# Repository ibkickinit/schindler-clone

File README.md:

# Schindler 2.0

A modern FPGA-based replacement for the Cal Media **Schindler MVPHD-24** — a 24fps video frame rate converter used to drive CRT monitors that appear in film shots. Roughly 75 MVPHD-24 units remain in service worldwide; this project is a from-scratch alternative scoped to modern workflows.

## Scope

- **Input:** HDMI + Composite + Component (with optional broadcast-tier SDI video IN/OUT/loop-through)
- **Output:** Composite + Component (YPbPr) + S-Video, driving 1970s consumer CRTs and broadcast monitors (Sony PVM/BVM); HDMI out for confidence monitoring or live output
- **Genlock:** to film camera reference (LTC, tri-level, black burst, word clock); SDI ref with VITC extraction
- **Frame rates:** 23.976, 24.000, 25.000, 29.97, 30.000, 47.95, 48.000, 50, 59.94, 60 fps (with 60 Hz → 50 Hz cadence conversion for cross-region content)
- **Color pipeline:** ported from the Screenie/NovaTool codebase
- **Control:** dual-band WiFi (concurrent AP + STA) + BLE setup pairing + GbE; web UI hosted on the Zynq PS under PetaLinux
- **Front panel:** 2.8-3.5" color TFT + rotary encoders + hardware buttons + status LEDs (no touchscreen)
- **Rear panel:** 2.2" color TFT (port status, 1Hz refresh) + port status LEDs (no touchscreen)
- 
## Why

The Schindler is unobtainable, expensive when found, and lacks modern color/EDID/web workflows. The market is small but underserved: rental houses, DPs shooting on CRTs, and music-video / period productions.

## Status

Early prototype phase, hardware ordered. See [`docs/01-spec.md`](docs/01-spec.md) for current spec & backlog and [`docs/schindler-playbook.md`](docs/schindler-playbook.md) for the development narrative.

## Hardware

### Development
- Digilent Zybo Z7-20 — FPGA bring-up (Zynq-7020 silicon, matches production target)
- STM32H735G-DK — UI MCU + TFT bench development
- Oscilloscope — signal analysis

### Production architecture
- Trenz TE0720 SOM — Zynq-7020 industrial (-40 to +85 °C), on custom carrier
- STM32H735IGT6 — dedicated front-panel UI MCU
- RP2040 + Si5351 — genlock PLL subsystem
- ADV7393 — composite/component/S-Video output DAC
- ADV7280 — composite/component input decoder
- Semtech GS3470 — SDI receiver (ref + optional broadcast video input)
- Semtech GS2962 — SDI transmitter (broadcast tier)
- Laird Sterling LWB5+ — pre-certified dual-band WiFi/BT module
- Custom 6-8 layer carrier PCB
- 1RU rack chassis

## License

TBD

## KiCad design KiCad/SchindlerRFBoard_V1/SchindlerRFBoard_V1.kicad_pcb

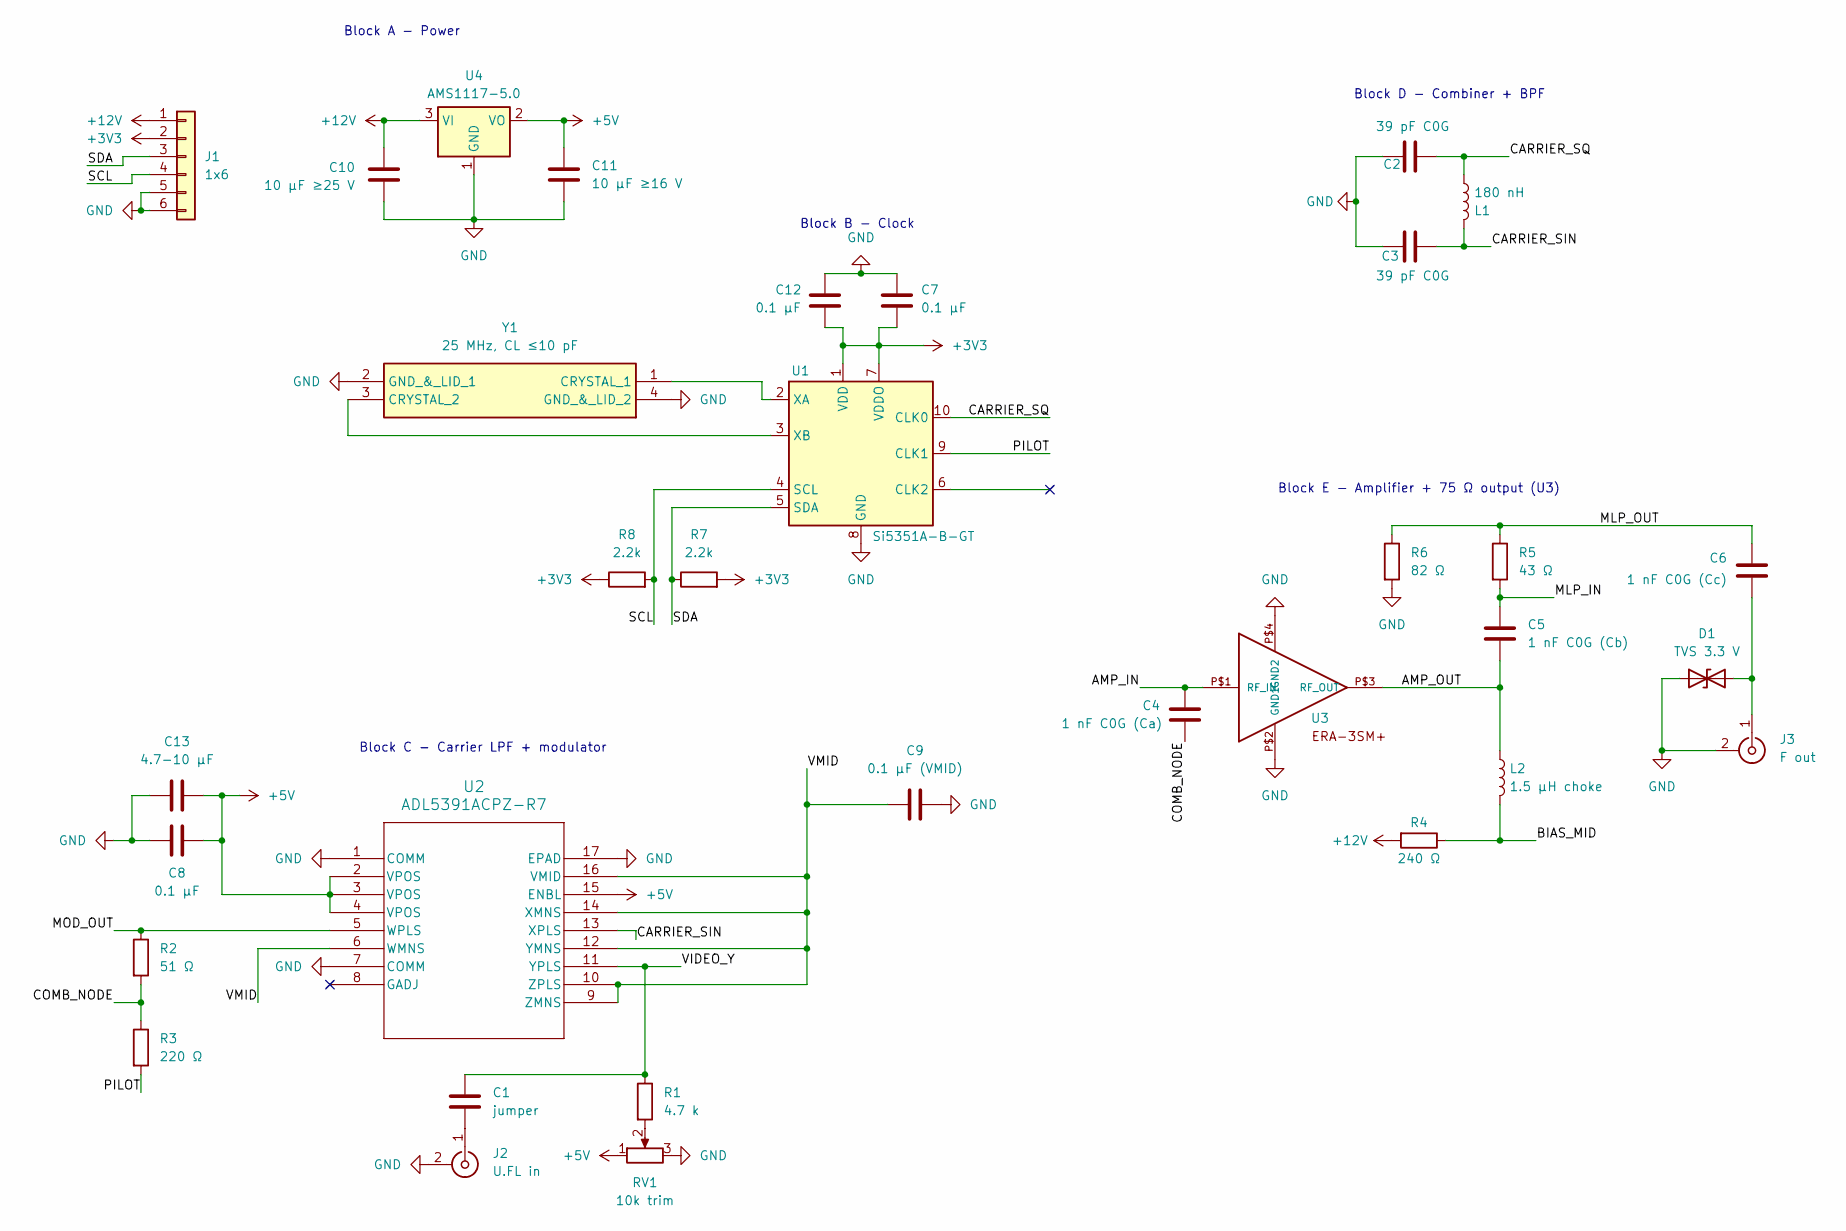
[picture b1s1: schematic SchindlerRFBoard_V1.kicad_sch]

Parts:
C1: jumper; C_0805_2012Metric
C2, C3: 39 pF C0G; C_0805_2012Metric
C4: 1 nF C0G (Ca); C_0805_2012Metric
C5: 1 nF C0G (Cb); C_0805_2012Metric
C6: 1 nF C0G (Cc); C_0805_2012Metric
C7, C8, C12: 0.1 µF; C_0805_2012Metric
C9: 0.1 µF (VMID); C_0805_2012Metric
C10: 10 µF ≥25 V; C_0805_2012Metric
C11: 10 µF ≥16 V; C_0805_2012Metric
C13: 4.7-10 µF; C_0805_2012Metric
D1: TVS 3.3 V; D_SOD-323
J1: 1x6; PinHeader_1x06_P1.00mm_Vertical
J2: U.FL in; U.FL_Hirose_U.FL-R-SMT-1_Vertical
J3: F out; U.FL_Hirose_U.FL-R-SMT-1_Vertical
L1: 180 nH; L_0805_2012Metric
L2: 1.5 µH choke; L_0805_2012Metric
R1: 4.7 k; R_0805_2012Metric
R2: 51 Ω; R_0805_2012Metric
R3: 220 Ω; R_0805_2012Metric
R4: 240 Ω; R_0805_2012Metric
R5: 43 Ω; R_0805_2012Metric
R6: 82 Ω; R_0805_2012Metric
R7, R8: 2.2k; R_0805_2012Metric
RV1: 10k trim; Potentiometer_Bourns_3296W_Vertical
U1: Si5351A-B-GT; MSOP-10_3x3mm_P0.5mm
U2: ADL5391ACPZ-R7; CP_16_27_ADI
U3: ERA-3SM+; WW107
U4: AMS1117-5.0; SOT-223-3_TabPin2
Y1: 25 MHz, CL ≤10 pF; LFXTAL072604; Manufacturer_Part_Number LFXTAL072604

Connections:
+3V3: C7.2, C12.2, J1.2, R7.2, R8.1, U1.1 (VDD), U1.7 (VDDO)
+5V: C8.1, C11.1, C13.1, RV1.1, U2.2 (VPOS), U2.3 (VPOS), U2.4 (VPOS), U2.15 (ENBL), U4.2 (VO)
+12V: C10.1, J1.1, R4.2, U4.3 (VI)
/AMP_IN: C4.2, U3.P$1 (RF_IN)
/AMP_OUT: C5.2, L2.1, U3.P$3 (RF_OUT)
/BIAS_MID: L2.2, R4.1
/CARRIER_SIN: C3.2, L1.2, U2.13 (XPLS)
/CARRIER_SQ: C2.1, L1.1, U1.10 (CLK0)
/COMB_NODE: C4.1, R2.2, R3.1
/MLP_IN: C5.1, R5.2
/MLP_OUT: C6.1, R5.1, R6.1
/MOD_OUT: R2.1, U2.5 (WPLS)
/PILOT: R3.2, U1.9 (CLK1)
/SCL: J1.4, R8.2, U1.4 (SCL)
/SDA: J1.3, R7.1, U1.5 (SDA)
/VIDEO_Y: C1.1, R1.1, U2.11 (YPLS)
/VMID: C9.1, U2.6 (WMNS), U2.9 (ZMNS), U2.10 (ZPLS), U2.12 (YMNS), U2.14 (XMNS), U2.16 (VMID)
GND: C2.2, C3.1, C7.1, C8.2, C9.2, C10.2, C11.2, C12.1, C13.2, D1.1 (A1), J1.5, J1.6, J2.2 (Ext), J3.2 (Ext), R6.2, RV1.3, U1.8 (GND), U2.1 (COMM), U2.7 (COMM), U2.17 (EPAD), U3.P$2 (GND1), U3.P$4 (GND2), U4.1 (GND), Y1.2 (GND_&_LID_1), Y1.4 (GND_&_LID_2)
unnamed: C6.2, D1.2 (A2), J3.1 (In)
unnamed: C1.2, J2.1 (In)
unnamed: R1.2, RV1.2
unnamed: U1.2 (XA), Y1.1 (CRYSTAL_1)
unnamed: U1.3 (XB), Y1.3 (CRYSTAL_2)

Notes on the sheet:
Block E - Amplifier + 75 Ω output (U3)
Block C - Carrier LPF + modulator
Block B - Clock
Block D - Combiner + BPF
Block A - Power

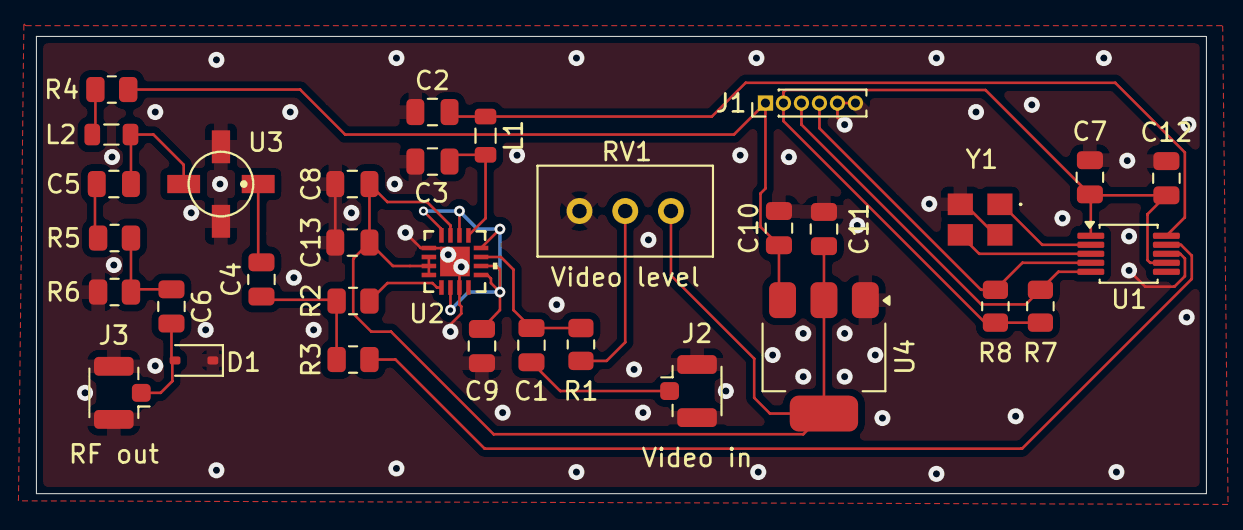
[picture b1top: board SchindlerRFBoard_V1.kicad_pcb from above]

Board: 2 copper layers, 65.0 x 25.4 mm, 33 parts (0 on the bottom side), 23 nets.

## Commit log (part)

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2026-06-04 docs(manifest): build #28 — Mackin blend engages on silicon (BLEND 60/60, DDR holds)
2026-06-05 fix(geometry): signed window translation (off-screen shift) + restore scale anchor
    Replaces #29's source-crop pan with the behavior actually requested:
    - Position is a SIGNED output-window origin: shift can push the image clean off
    the left/top edge (pixels leave the frame, matte fills the opposite edge), at
    ANY scale incl. 100%. pg_addrgen membership compares are now signed.
    - src_col0/src_row0 become the DDA seed = source col/row at the first on-screen
    pixel; firmware derives it from the off-screen amount. Same formula yields the
2026-06-05 docs(manifest): build #31 ✅ CLEAN 3-boot — closes owed #28 Mackin; #30 verified; #106 gate clear
2026-06-05 fix(daemon): send 'P' flip cmd only on flip change — kills redundant 2nd geometry write during size/shift drags
2026-06-05 fix(#110): color-temp neutral = D65 6500K (video/display white), not 5600 — rebalance ladder around D65
2026-06-05 fix(#111): Freeze un-freeze — re-arm S2MM VSIZE on resume (RS alone doesn't restart a halted VDMA)
2026-06-05 feat(#112 Phase-3): wire gamma_lut into color pipeline + load path + presets
    BD: splice gamma_lut_0 after color_matrix_0 -> axis_to_vid_io_0 (build_phase_b); add gamma
    load GPIO axi_gpio_11 @ M14 (NUM_MI 14->15) + slices (bypass/tog/ch/addr/data) wired to
    gamma_lut_0 (readengine_b_bd). Firmware: GAMMA_GPIO_BASE + gamma 1.8/2.2/2.4 preset LUTs
    (precomputed, libm-free) + toggle-strobed loader + 'O g <0|18|22|24>'. Daemon operator.set
    gamma; UI Gamma Off/1.8/2.2/2.4 buttons. Default GPIO bypass=1 (transparent at boot).
    YCbCr matrix preset deferred (analog-only, would break HDMI RGB; trivial future color_matrix preset).
2026-06-05 fix(#112): gamma — on-device fixed-point curve, kill bulk UART transport (corruption fix)
    The bulk LUT load ('O G' 262-char line) corrupted under the periodic status-print bursts
    that block the UART poll → RX FIFO overflow → garbage curve (crush+speckle). Replace with
    on-device fixed-point pow: daemon sends only 'O g <gamma*10>' (short, robust); firmware
    computes out[i]=round(255*(i/255)^(1/g)) via Q16 integer-power + iterated-sqrt. Verified
    <=1 LSB vs float pow (g 0.5..4.0). Removed preset tables, bulk 'O G' handler, hexnib.
    Slider + presets unified on 'O g'. ELF-only (gamma_lut HDL unchanged).
2026-06-05 docs(manifest): record builds #32 (flips) / #33 (gamma, failed timing) / #34 (gamma clean) + ELF turns + open #114 read-engine gradient chroma
2026-06-05 docs(#108): 720p60-OUT column 1080-input cells verified — 1080p24→720p60 ✅ (3-boot), 1080p30→720p60 ✅; full Osee sweep (24/30/60 + 59.94/29.97 NTSC + 50/25 PAL) all lock w/ correct cadence + zero dri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
2026-06-06 fix(#114): double-buffer gamma_lut — atomic SOF bank-swap kills load chroma + restores live-drag
    Root cause (re-attributed from read engine): single-buffer loaded the LUT over the live display
    with non-atomic per-address R/B/G writes → fast/large change showed a half-updated chromatic LUT.
    Now: 2 banks (addr={bank,idx}), firmware loads the INACTIVE bank at any speed (display untouched),
    flips swap → bank goes live ATOMICALLY at next SOF. No flash, no chroma, live-drag safe.
    HDL gamma_lut.v (swap input + sof-gated rd_bank) + TB (Total errors=0: loads don't change display,
    swap only at SOF, ping-pong). Firmware gamma_put/gamma_set_byp_swap (load-to-inactive then enable+swap).
2026-06-06 feat(#107a): wire filt_mode + inv_w GPIO — firmware reciprocal + UART F 0|1|2|3
    BD: filt_h(bit27)→filt_mode GEO_C ch2 [31:30]; new axi_gpio_12 @ M15 (NUM_MI 15→16) inv_w[15:0]
    (inv_h[31:16] reserved for #107b) → pg_re_0/inv_w. Firmware: g_re_filt_mode (0..3); re_write_geometry
    computes inv_w=round((1<<16)/w) clamp 0xFFFF + writes axi_gpio_12; UART 'F 0|1|2|3' (NN/box/H-bilin/H+V).
    Completes #107a (H-bilinear) — bundle w/ #114 into next bitstream; check lerp WNS (pipeline if <0).
2026-06-06 fix(#107a): add stage R0 (register taps before lerp) — WNS -5.6 path was m3_rd_data→lerp→r_A
    #36 still failed (-5.6): the lerp fed off m3_rd_data which already carries linefetch window-extract
    combinational depth. R0 registers the raw taps + weight first, so the lerp (stage R) starts from
    registers (one multiply to r_A). +1 more ospace reserve (now 7). Sim Total errors=0. Rebuilding.
2026-06-06 feat(#114): restore live-drag gamma slider — load is race-free now, drag = clean atomic loads
    Re-enables debounced 'input' commit (live preview) now that the data-then-strobe CDC + double-buffer
    make every load reliable + atomic. Re-archived 38-720p60-gamma-bilinear with the fixed ELF (bench-validated:
    Justin confirms gamma chroma GONE, bilinear clean). Closes the #114 chroma saga.
2026-06-06 feat(#107b): BD inv_h slice (axi_gpio_12[31:16] → pg_re_0/inv_h) for V-bilinear weight
2026-06-06 feat(ui): 'Engine 1 path' reorg + maintain-aspect-ratio lock
    Reorganize the page to mirror the silicon signal chain:
    Source/Input (input range/colorspace) → Engine 1 → Output A (HDMI): Geometry&Scale · FRC · Color · Operator
    Color Temp moves into the Color group (it's the color_correct white-point, not the read engine) alongside
    the catalog Saturation/RGB/matrix + gamma — answering 'merge the color-related things'. Per-category named
    mounts (mount-color/frc/scaler) let the firmware-catalog controls render inside the matching Engine-1
    sub-group; System/Status fall back to #catalog-mount. Dual-engine build will add a parallel 'Engine 2 → Output B'.
2026-06-06 design(corrections): validate keystone + warp math (previewer) — all three proven
    tools/correction_preview.py renders keystone (projective, per-pixel /w divide → clean perspective
    trapezoid) and warp (9x9 mesh sampling the pincushion map → reproduces the parametric render, proving
    the mesh subsumes the parametric corrections). Same (ox,oy)->(sx,sy) addrgen interface as the real
    engine. All three correction maths now visually verified pre-HDL; addrgen settled, only the deferred
    engine HDL remains. Validation status recorded in the design doc.
2026-06-07 docs(engine): phased warp-engine build tracker + pg_tilecache architecture spec
    Phase 1 (pg_affine) done; Phase 2 (pg_tilecache) fully specified: tag/LRU + tile BRAM + prefetch
    walker (runs the affine DDA ahead) + AXI DataMover tile DMA + 2x2 sampler + underrun guard. 128-tile/
    384KB cache, 32x32 tiles (gate params). Phase-2 sim with a behavioral DDR = the real-time gate (assert
    output FIFO never underruns + bit-exact warp). Risks/knobs noted. Phase 5b = pincushion/keystone/warp
    addrgen variants (math pre-validated).
2026-06-07 feat(engine P2/M3a): 4-bank 1px/clock 2x2 gather — bit-exact in sim
    The hard part: returns the bilinear 2x2 in ONE cycle even across 4 tiles, via a 4-bank (x-parity x
    y-parity) tile BRAM where each parity-bank supplies exactly one neighbour; a parity mux routes banks
    to p00/p10/p01/p11, with an edge-mux for clamp-to-self frame edges. sim/pg_tilecache_rt_tb.v: 3072
    gathers over 2 passes (straddles + edges + cache hits) = 0 errors. Bug found+fixed: tag lookup was a
    function in a wire-assign (sensitive only to its arg, NOT the tag/vld arrays it reads -> fills never
    re-triggered it -> infinite re-fetch). Combinational always@* fixes it. LESSON: never put a memory-
2026-06-07 feat(engine M3c): full warp datapath integrated + end-to-end bit-exact in RTL
    pg_warp_engine = dual pg_affine (consumer + prefetch, bounded lead) -> pg_tilecache_rt2 -> 2-stage
    bilinear -> AXIS out. pg_affine rewritten as a proper ready/valid producer (the pulse-valid version
    dropped coords when the cache stalled -> frac/pixel skew). Lead bound added so the round-robin victim
    never evicts an unconsumed tile. Sim (pg_warp_engine_tb, rot20, behavioral 2x2-block DMA): o_pix
    bit-exact vs an affine-bilinear golden, 36864 px in 38376 cyc (< frame period). Bugs fixed: affine
    handshake, prefetch eviction race, + 2 TB-golden bugs (8-bit subtract wrap in lerp, edge-clamp window
2026-06-07 feat(engine M4): skid buffers break the affine<->cache handshake loop (timing)
    OOC4 left WNS -3.477 on cache py_ -> affine ox: the affine's o_ready was gated by the live tag
    lookup (pf_ready), so the DDA adder sat in a combinational loop with the lookup. pg_skid (AXIS
    register slice, s_ready depends only on internal state) between each affine and the cache port
    decouples it -> affine advance gated by a register, not the lookup. Re-verified bit-exact
    (pg_warp_engine_tb rot20: 0 err, real-time). Final OOC (timing) in flight.
2026-06-07 feat(engine M4): pg_tile_dma — tile fetch + 2x2 reorder; real fill path bit-exact
    Cache fetch_req(tx,ty) -> 16 row-fetches via the existing DataMover fetch/beat interface -> pg_unpack
    (64b beats -> 24b px) -> buffer even row, pair with odd -> 64 2x2-block fills. Integration TB
    (pg_warp_dma_tb: warp engine + tile_dma + behavioral DataMover) is BIT-EXACT vs golden through the
    real fill path. BUT not yet real-time: 65818 > 56100 cyc — pg_unpack emits 1 px/clk, so a tile fills
    in ~256 clk vs the M3b block-fill model's 64; fill rate ~= gather rate leaves no prefetch lead. Fix
    next: wider unpack (~2.5 px/clk, within the 64b-beat bandwidth) +/- V-blank warmup modeling (M2 lesson).
2026-06-07 docs(engine): M4 fill-path integration real-time+bit-exact; BD swap + firmware + build remain
2026-06-07 test(engine): real-fill transform sweep — hard transforms starve (review confirmed)
    pg_warp_dma_tb now sweeps rot20/rot45/shrink1.5/aniso30 through the real set-assoc cache + real fill.
    rot20 PASS; rot45/shrink/aniso FAIL (40/94/83% underrun, bit-err=0 = pure starve). Root cause: single-
    in-flight ~128cyc/tile fill (2px/clk gearbox) can't feed high-tile-cross transforms in bursts; set-
    conflict aliasing secondary (hash helped shrink, broke rot20 -> reverted). Not bench-ready for arbitrary
    geometry. Findings + fix path in docs/warp-realfill-sweep.md. (Reverted the hash; kept plain set index.)
2026-06-07 docs(engine): handoff prompt for fresh-context agent — fill rework is next (capacity done)
2026-06-07 docs(engine): round-3 TL;DR — real-geometry RESOLVED, real-time at 1080p
2026-06-08 docs(engine): refined prefetch pipelining plan (feedforward-first, hazard only in suffix) + NO_ILA constraint + bitstream non-functional warning
2026-06-08 docs(engine): avm-snapshot design note — naive precompute is stale (shared tiles), needs CAM bypass
2026-06-08 docs(engine): handoff #2 — SCOPE: warp must support 1080p OUTPUT (148.5MHz/6.7ns); re-target timing, 720p numbers don't transfer
2026-06-10 feat(orient): web GUI — cardinal orientation buttons (0/90/180/270) replace rotation slider
    The production engine is the 4 cardinal orientations, not free rotation, so buttons (not a -180..180
    slider) are the right control. Each button sends warp.set {deg} immediately; active one highlights.
2026-06-10 docs(orient): bench findings — warp cache starves full-frame read; direct buffer needed
    Telemetry-proven: fit (8160 tiles) starves NTILE=256 (starved=12107, no LEAD fixes it; best 12288
    =7575, 16384 freezes). 1:1 crop (3600 tiles) hid it. Firmware fit(90/270)+pan fixes are correct and
    stay; the associative cache must be replaced by a sequential streaming buffer (the production-final).
2026-06-10 feat(orient): integrate tile-order engine + pg_tile_to_raster in pg_warp_top; BD NTILE=64
    pg_warp_top: engine(tile-order) -> pg_tile_to_raster -> line-FIFO -> m_axis (SOF tag = r_tu).
    BD: NTILE 256->64 (tile-order needs only an output tile's source -> ~11 BRAM, frees room for the
    28-BRAM reorder band; ~135/140 total), LEAD 2048->1024. Added pg_affine_tile.v + pg_tile_to_raster.v
    to build. pg_warp_top elaborates clean. This is the starvation-free full-frame fix.
2026-06-10 docs(orient): bench — tile-order solves working-set; DMA throughput is the remaining wall
    Frame completes (opix 921600) but residual progressive starvation (DMA throughput, not lead) ->
    0deg top-clean/wrap+bottom-tear, 90/180/270 worse (strided transpose). Next: DMA read coalescing
    (merge contiguous tile bursts) + column-major tiles for transpose + maybe bypass line-FIFO.
2026-06-25 docs: W1-A done (runtime tiler geometry sim-proven), W1-B/C next
